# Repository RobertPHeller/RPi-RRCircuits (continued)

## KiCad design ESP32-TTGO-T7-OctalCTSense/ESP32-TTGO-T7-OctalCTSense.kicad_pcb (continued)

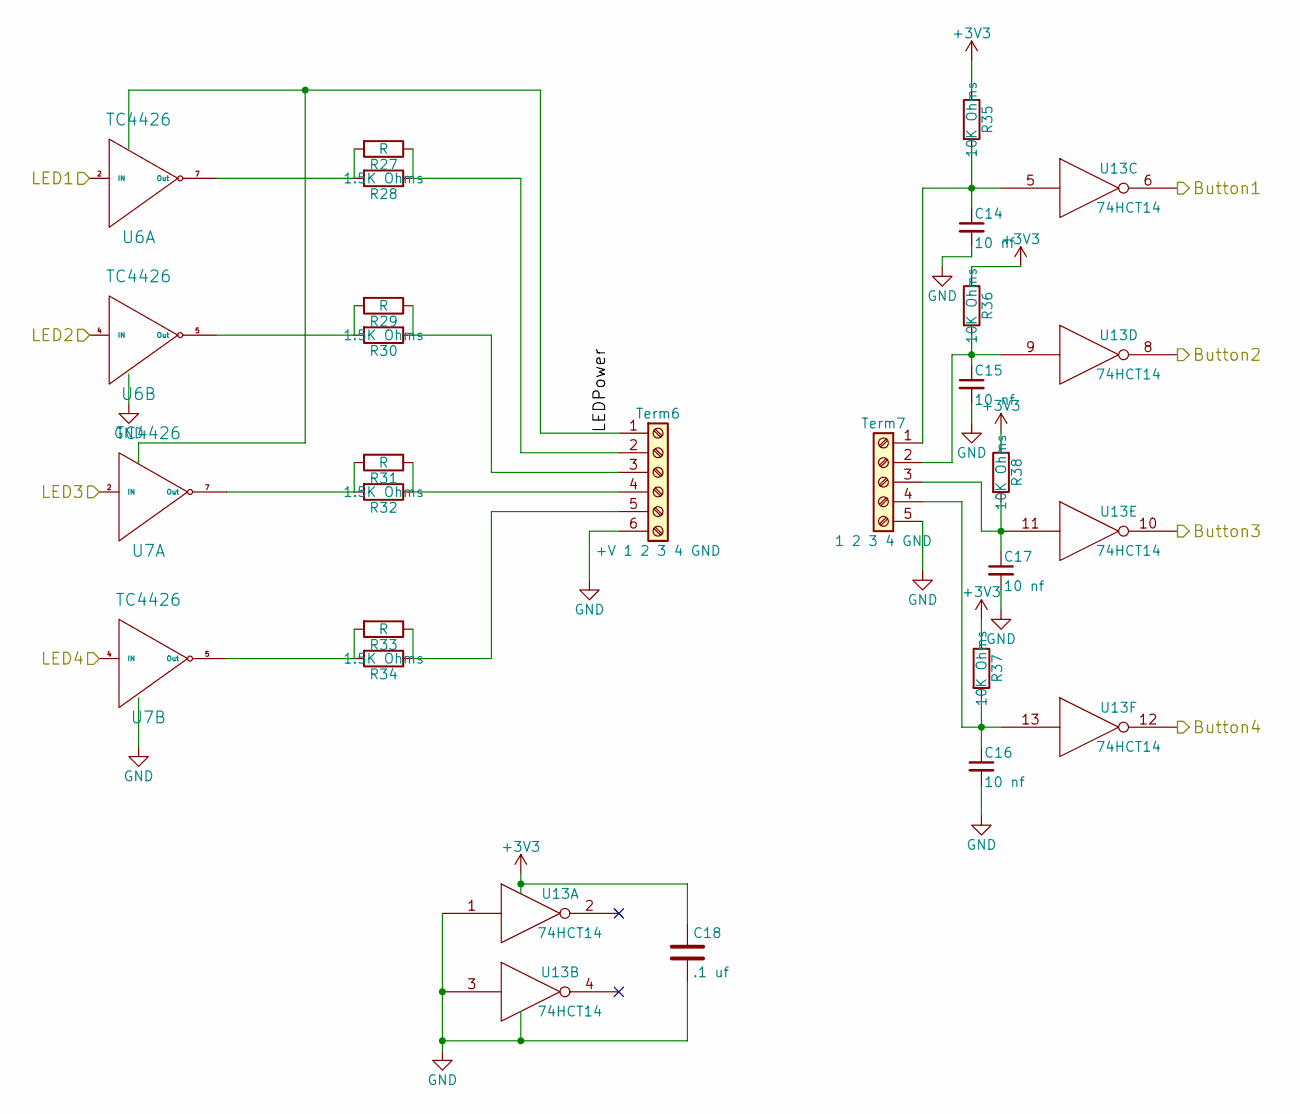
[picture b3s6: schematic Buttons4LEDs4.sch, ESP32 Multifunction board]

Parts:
C14, C15, C16, C17: 10 nf; C_0603; Mouser Part Number 710-885382206002
C18: .1 uf; C_0603
R27, R29, R31, R33: R; R_Axial_DIN0207_L6.3mm_D2.5mm_P7.62mm_Horizontal
R28, R30, R32, R34: 1.5K Ohms; R_0603; Mouser Part Number 71-CRCW06031K50JNEAC
R35, R36, R37, R38: 10K Ohms; R_0603; Mouser Part Number 71-CRCW060310K0JNEBC
Term6: +V 1 2 3 4 GND; TerminalBlock_Pheonix_MPT-2.54mm_6pol; Mouser Part Number 651-1725698
Term7: 1 2 3 4 GND; TerminalBlock_Pheonix_MPT-2.54mm_5pol; Mouser Part Number 651-1725685
U6, U7: TC4426; SOIC-8_3.9x4.9mm_Pitch1.27mm
U13: 74HCT14; SOIC-14_3.9x8.7mm_Pitch1.27mm; Mouser Part Number 595-CD74HC14M

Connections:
/Button_1: U13.6; also elsewhere on the board
/Button_2: U13.8; also elsewhere on the board
/Button_3: U13.10; also elsewhere on the board
/Button_4: U13.12; also elsewhere on the board
/LED_1: U6.2 (IN); also elsewhere on the board
/LED_2: U6.4 (IN); also elsewhere on the board
/LED_3: U7.2 (IN); also elsewhere on the board
/LED_4: U7.4 (IN); also elsewhere on the board
GND: C14.2, C15.2, C16.2, C17.2, C18.2, Term6.6, Term7.5, U6.3 (GND), U7.3 (GND), U13.1, U13.3, U13.7 (GND); also elsewhere on the board
unnamed: C14.1, R35.2, Term7.1, U13.5
unnamed: C15.1, R36.2, Term7.2, U13.9
unnamed: C16.1, R37.2, Term7.4, U13.13
unnamed: C17.1, R38.2, Term7.3, U13.11
unnamed: R27.1, R28.1, Term6.2
unnamed: R27.2, R28.2, U6.7 (Out)
unnamed: R29.1, R30.1, Term6.3
unnamed: R29.2, R30.2, U6.5 (Out)
unnamed: R31.1, R32.1, Term6.4
unnamed: R31.2, R32.2, U7.7 (Out)
unnamed: R33.1, R34.1, Term6.5
unnamed: R33.2, R34.2, U7.5 (Out)
Vdd: Term6.1, U6.6 (Vdd), U7.6 (Vdd)

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
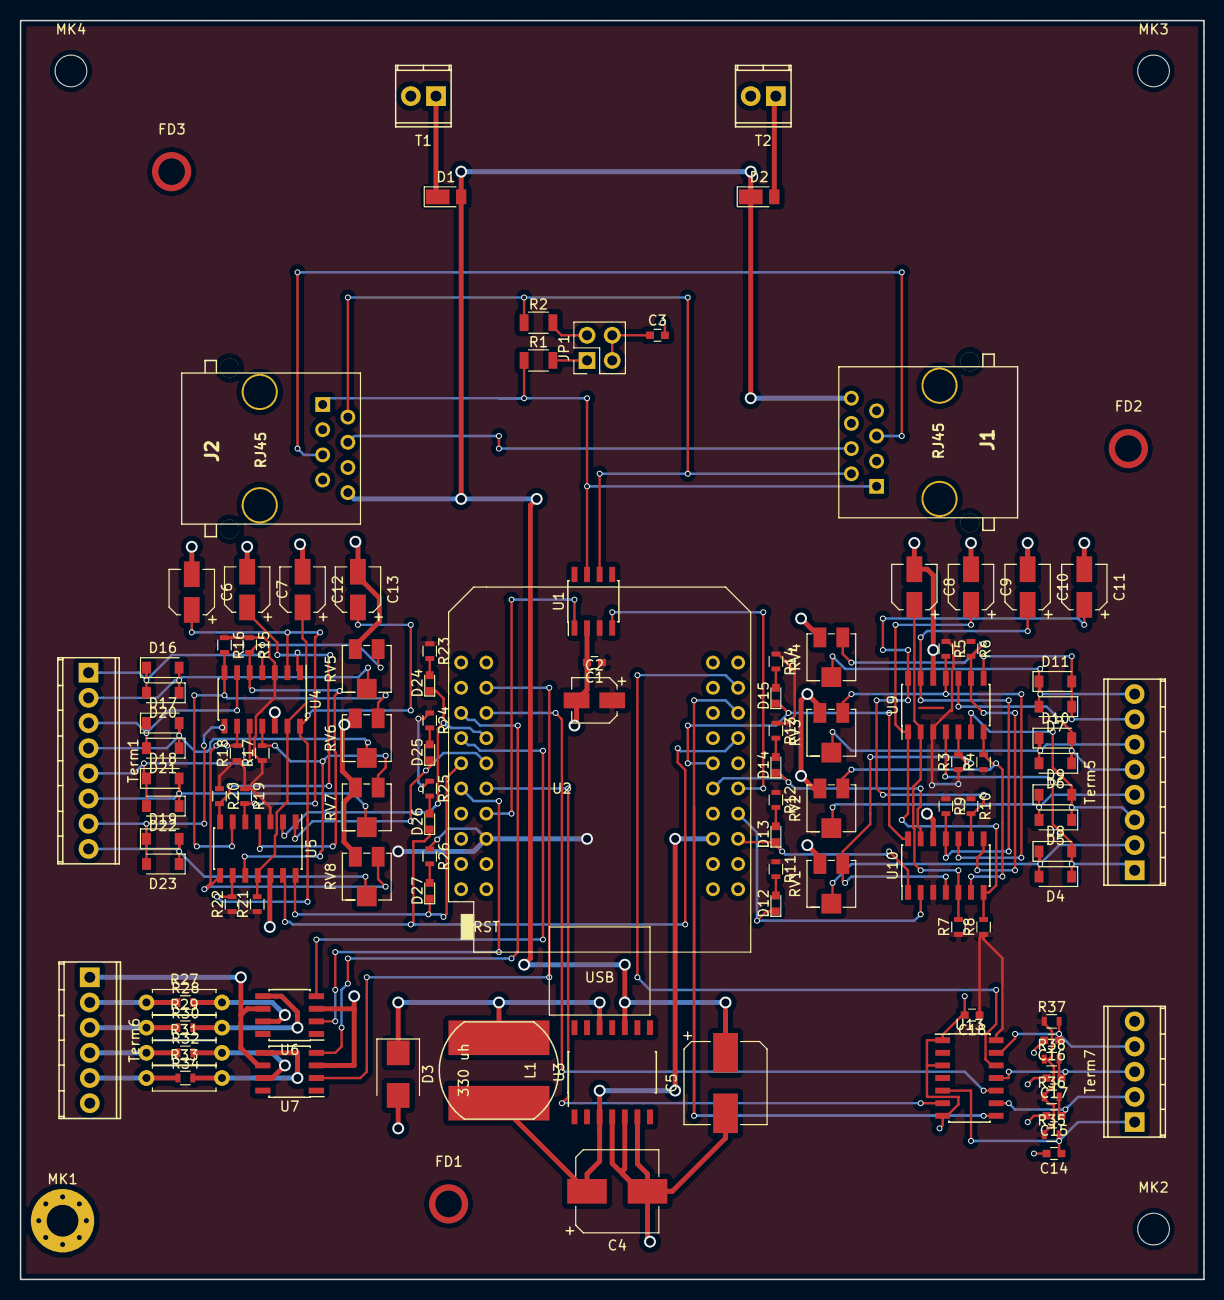
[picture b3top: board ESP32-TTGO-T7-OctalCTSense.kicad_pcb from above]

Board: 2 copper layers, 119.4 x 127.0 mm, 118 parts (0 on the bottom side), 85 nets.

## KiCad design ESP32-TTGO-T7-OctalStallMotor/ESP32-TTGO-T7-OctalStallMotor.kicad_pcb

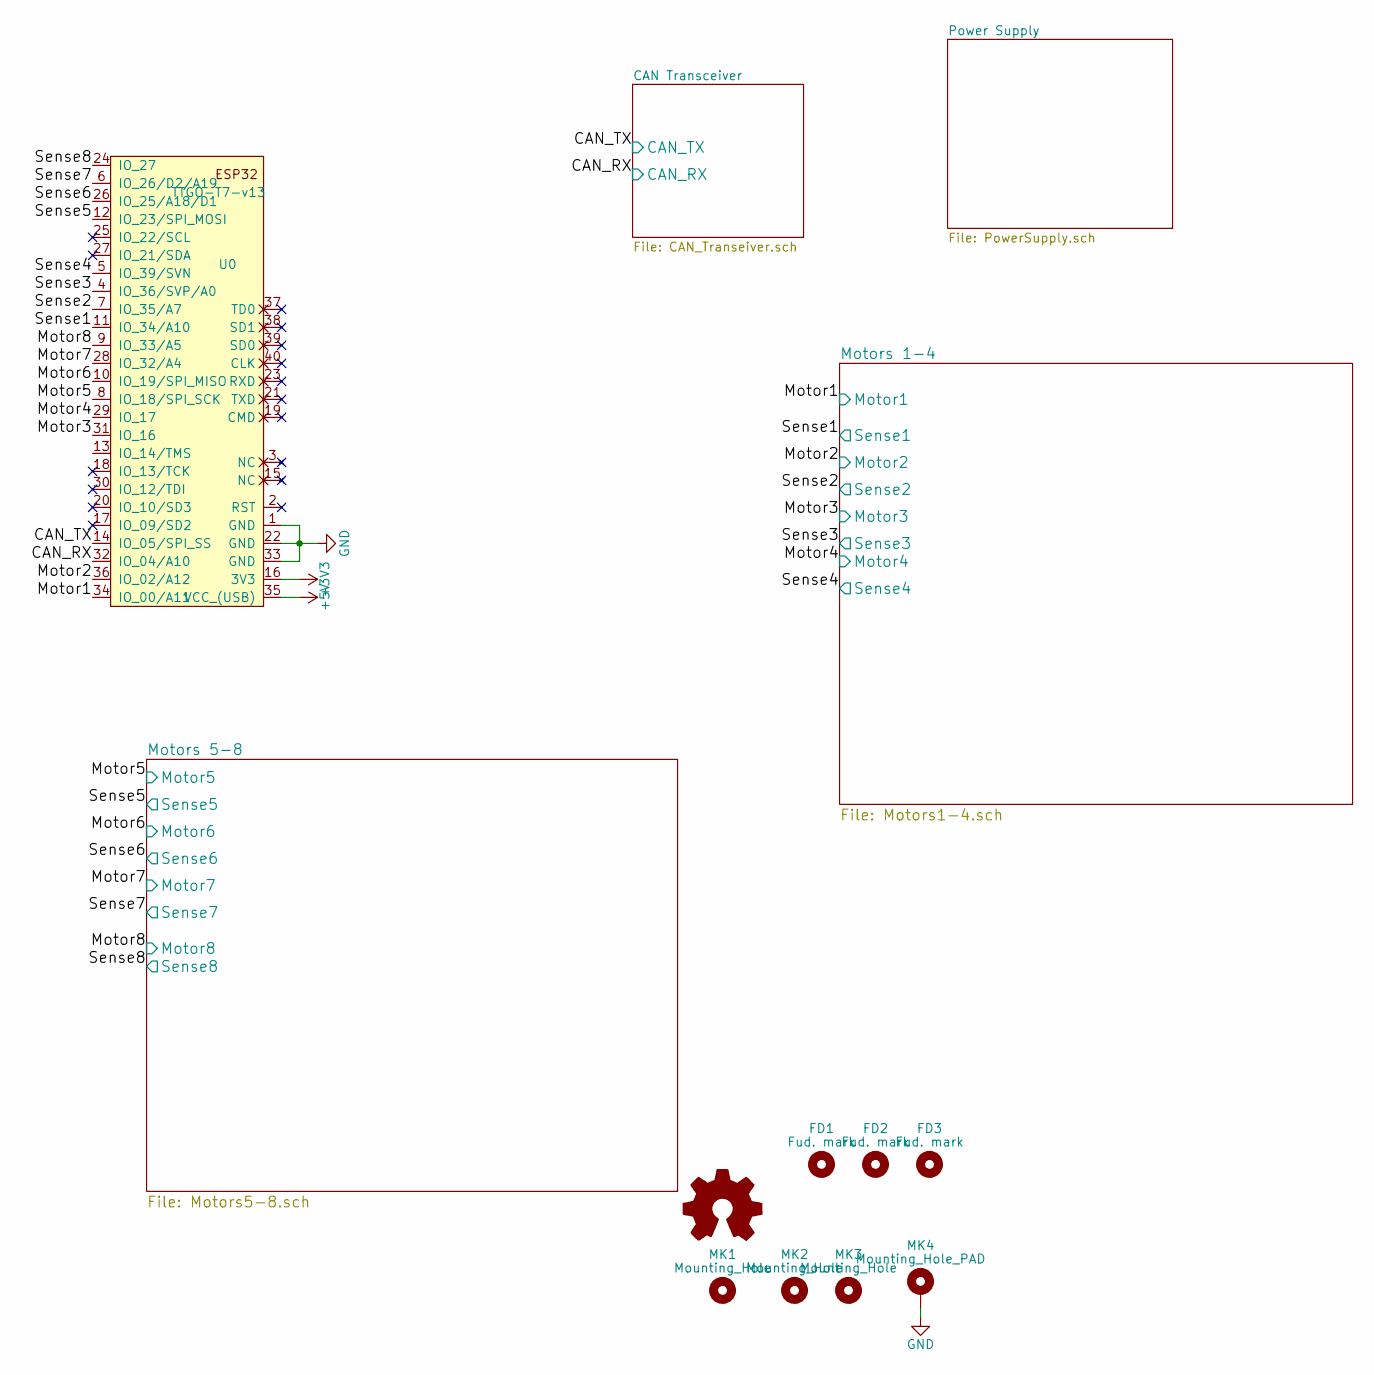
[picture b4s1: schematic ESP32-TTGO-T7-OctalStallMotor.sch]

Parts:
FD1, FD2, FD3: Fud. mark; Fiducial_Modern_CopperTop
MK1, MK2, MK3: Mounting_Hole; MountingHole_3.2mm_M3
MK4: Mounting_Hole_PAD; MountingHole_3.2mm_M3_Pad_Via
U0: TTGO-T7-v13; ESP32_mini

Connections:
+5V: U0.35 (VCC_(USB)); also elsewhere on the board
/CAN_RX: U0.32 (IO_04/A10); also elsewhere on the board
/CAN_TX: U0.14 (IO_05/SPI_SS); also elsewhere on the board
/Motor1: U0.34 (IO_00/A11); also elsewhere on the board
/Motor2: U0.36 (IO_02/A12); also elsewhere on the board
/Motor3: U0.31 (IO_16); also elsewhere on the board
/Motor4: U0.29 (IO_17); also elsewhere on the board
/Motor5: U0.8 (IO_18/SPI_SCK); also elsewhere on the board
/Motor6: U0.10 (IO_19/SPI_MISO); also elsewhere on the board
/Motor7: U0.28 (IO_32/A4); also elsewhere on the board
/Motor8: U0.9 (IO_33/A5); also elsewhere on the board
/Sense1: U0.11 (IO_34/A10); also elsewhere on the board
/Sense2: U0.7 (IO_35/A7); also elsewhere on the board
/Sense3: U0.4 (IO_36/SVP/A0); also elsewhere on the board
/Sense4: U0.5 (IO_39/SVN); also elsewhere on the board
/Sense5: U0.12 (IO_23/SPI_MOSI); also elsewhere on the board
/Sense6: U0.26 (IO_25/A18/D1); also elsewhere on the board
/Sense7: U0.6 (IO_26/D2/A19); also elsewhere on the board
/Sense8: U0.24 (IO_27); also elsewhere on the board
GND: MK4.1, U0.1 (GND), U0.22 (GND), U0.33 (GND); also elsewhere on the board

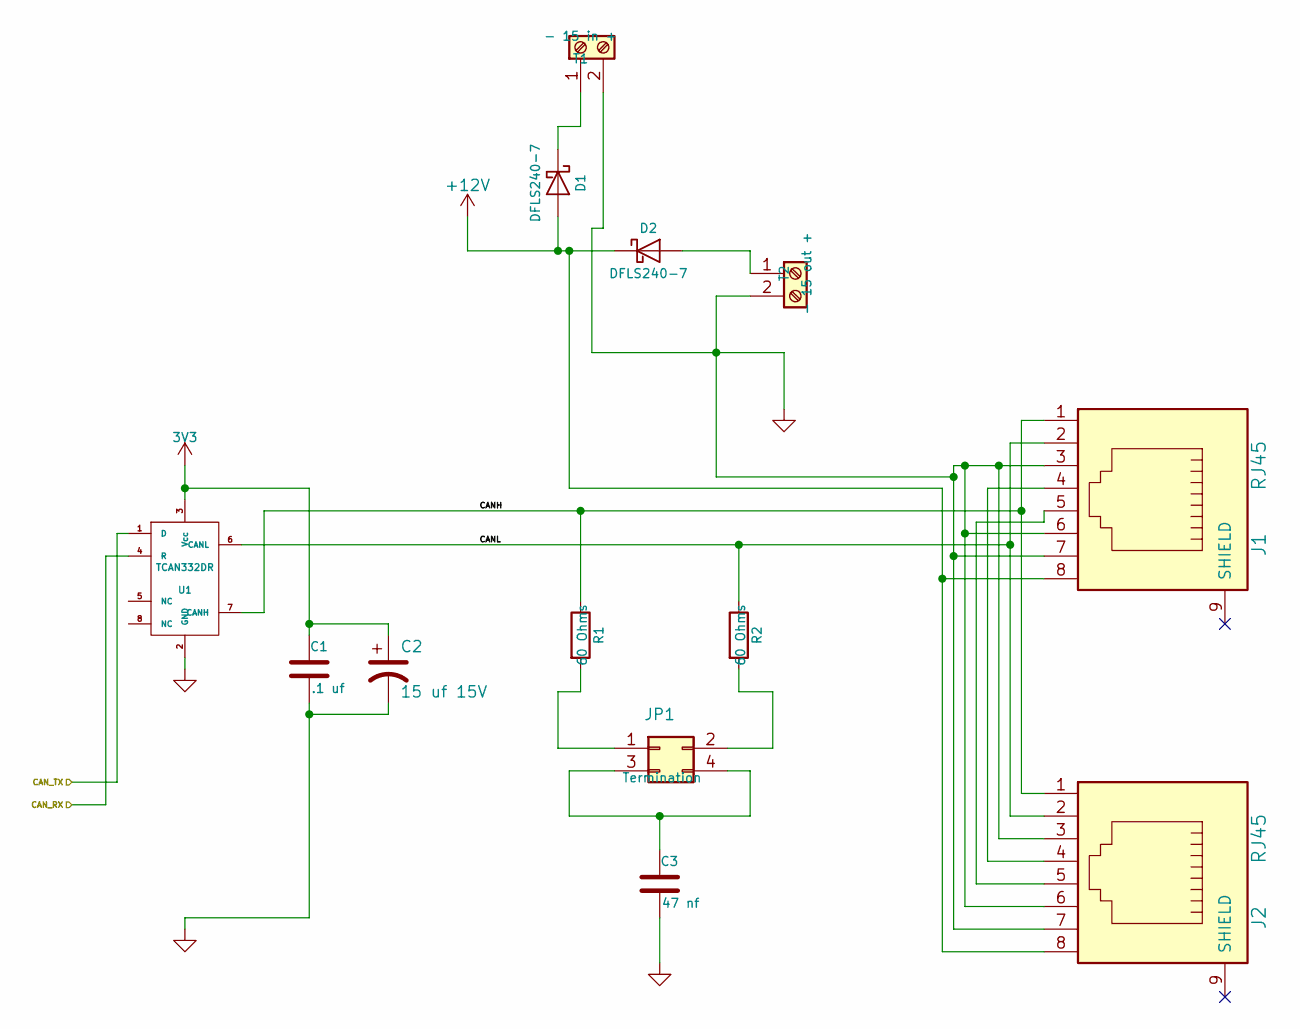
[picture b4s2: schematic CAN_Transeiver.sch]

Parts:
C1: .1 uf; C_0603; Mouser Part Number 710-885012206095
C2: 15 uf 15V; CP_Elec_4x5.7; Mouser Part Number 647-UUD1C150MCL
C3: 47 nf; C_0603; Mouser Part Number 710-885012206093
D1, D2: DFLS240-7; D_PowerDI-123; Mouser Part Number 621-DFLS240-7
J1, J2: RJ45; RJ45_8N-S; Mouser Part Number 710-615008144221
JP1: Termination; Pin_Header_Straight_2x02_Pitch2.54mm; Mouser Part Number 649-67997-404HLF
R1, R2: 60 Ohms; R_1206; Mouser Part Number 71-CRCW120660R0KNAIF
T1: - 15 in +; TerminalBlock_Pheonix_MPT-2.54mm_2pol; Mouser Part Number 651-1725656
T2: - 15 out +; TerminalBlock_Pheonix_MPT-2.54mm_2pol; Mouser Part Number 651-1725656
U1: TCAN332DR; SOIC-8_3.9x4.9mm_Pitch1.27mm; Mouser Part Number 595-TCAN332DR

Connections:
+12V: D1.2 (A), D2.1 (K), J1.8, J2.8; also elsewhere on the board
/CAN Transceiver/CANH: J1.1, J2.1, R1.1, U1.7 (CANH)
/CAN Transceiver/CANL: J1.2, J2.2, R2.1, U1.6 (CANL)
/CAN_RX: U1.4 (R); also elsewhere on the board
/CAN_TX: U1.1 (D); also elsewhere on the board
GND: C1.2, C2.2, C3.2, J1.3, J1.6, J1.7, J2.3, J2.6, J2.7, T1.2, T2.2, U1.2 (GND); also elsewhere on the board
unnamed: C3.1, JP1.3, JP1.4
unnamed: D1.1 (K), T1.1
unnamed: D2.2 (A), T2.1
unnamed: J1.4, J2.4
unnamed: J1.5, J2.5
unnamed: JP1.1, R1.2
unnamed: JP1.2, R2.2

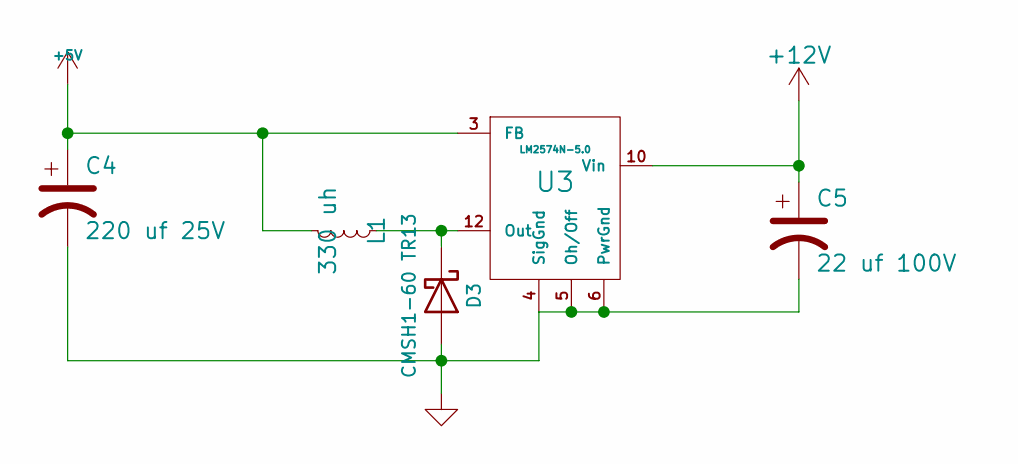
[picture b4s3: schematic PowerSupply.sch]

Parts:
C4: 220 uf 25V; CP_Elec_8x10; Mouser Part Number 647-UWT1E221MNL1GS
C5: 22 uf 100V; CP_Elec_8x10; Mouser Part Number 647-UUX2A220MNL6GS
D3: CMSH1-60 TR13; D_SMB; Mouser Part Number 610-CMSH1-60TR13
L1: 330 uh; SRN1060; Mouser Part Number 652-SRN1060-331M
U3: LM2574N-5.0; SOIC-14_7.4x8.7mm_Pitch1.27mm; Mouser Part Number 926-LM2574N-5.0/NOPB

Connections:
+5V: C4.1, L1.2, U3.3 (FB); also elsewhere on the board
+12V: C5.1, U3.10 (Vin); also elsewhere on the board
GND: C4.2, C5.2, D3.2 (A), U3.4 (SigGnd), U3.5 (Oh/Off), U3.6 (PwrGnd); also elsewhere on the board
unnamed: D3.1 (K), L1.1, U3.12 (Out)

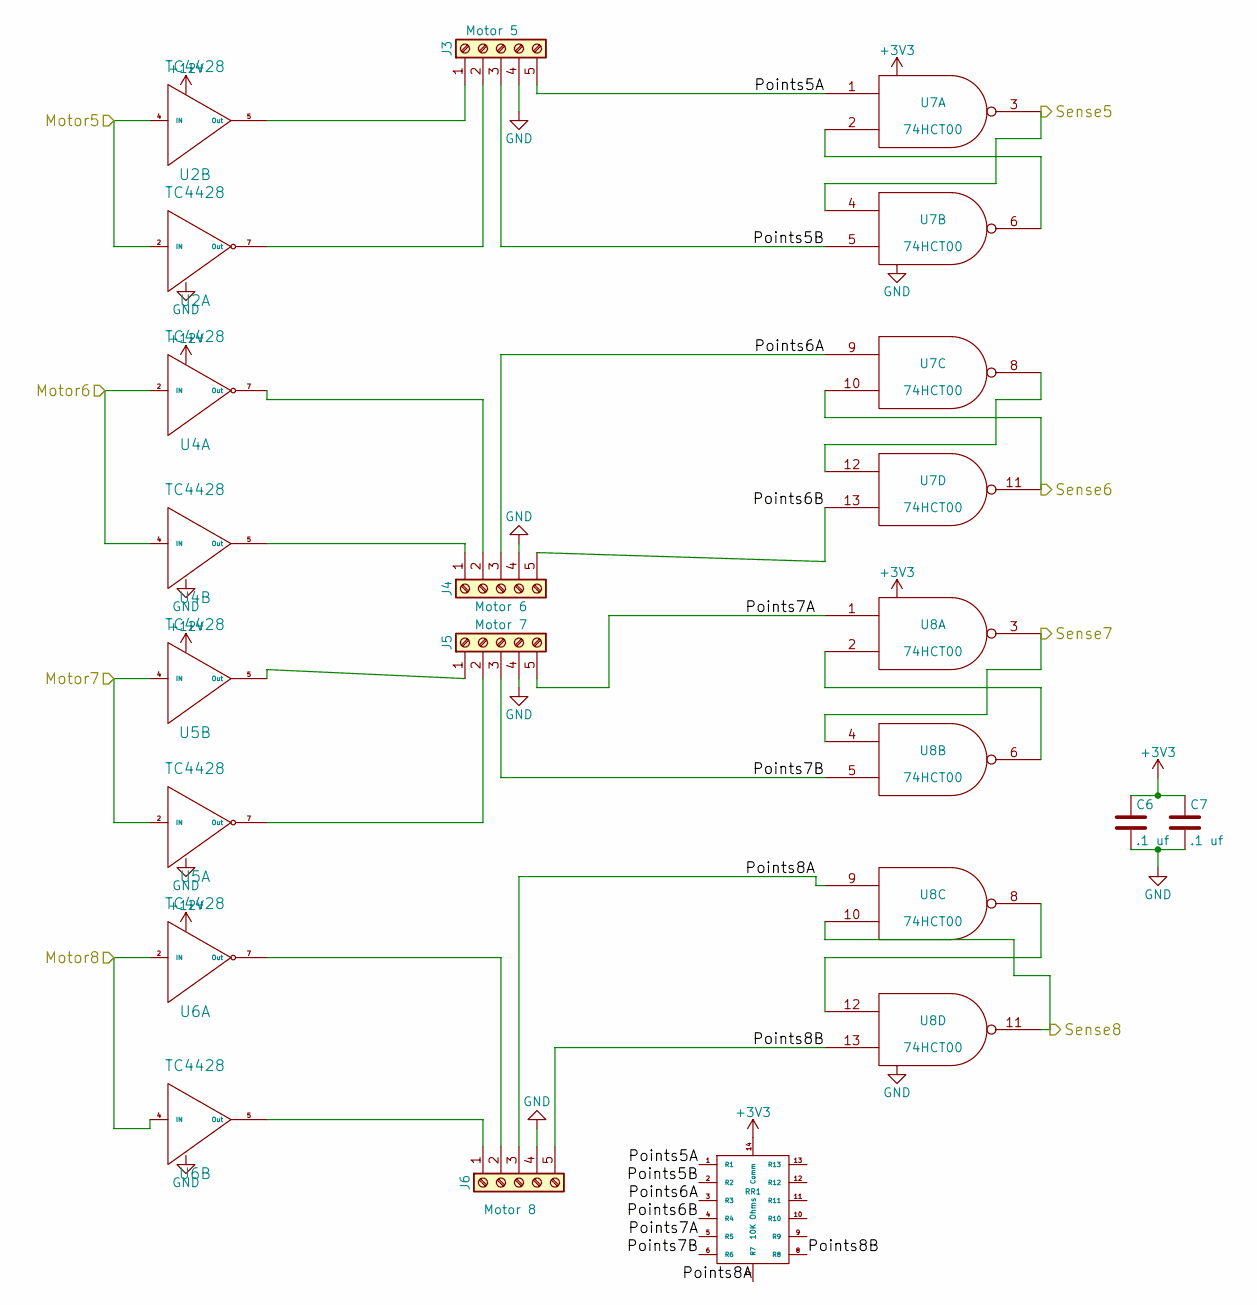
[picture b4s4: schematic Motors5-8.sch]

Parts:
C6, C7: .1 uf; C_0603; Mouser Part Number 710-885012206095
J3: Motor 5; TerminalBlock_Pheonix_MPT-2.54mm_5pol; Mouser Part Number 651-1725685
J4: Motor 6; TerminalBlock_Pheonix_MPT-2.54mm_5pol; Mouser Part Number 651-1725685
J5: Motor 7; TerminalBlock_Pheonix_MPT-2.54mm_5pol; Mouser Part Number 651-1725685
J6: Motor 8; TerminalBlock_Pheonix_MPT-2.54mm_5pol; Mouser Part Number 651-1725685
RR1: 10K Ohms; 4814P; Mouser Part Number 652-4814P-T2LF-10K
U2, U5: TC4428; SOIC-8_3.9x4.9mm_Pitch1.27mm; Mouser Part Number 579-TC4428VOA
U4, U6: TC4428; SOIC-8_3.9x4.9mm_Pitch1.27mm
U7, U8: 74HCT00; SOIC-14_3.9x8.7mm_Pitch1.27mm; Mouser Part Number 595-SN74AHC00D

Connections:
+12V: U2.6 (Vdd), U4.6 (Vdd), U5.6 (Vdd), U6.6 (Vdd); also elsewhere on the board
/Motor5: U2.2 (IN), U2.4 (IN); also elsewhere on the board
/Motor6: U4.2 (IN), U4.4 (IN); also elsewhere on the board
/Motor7: U5.2 (IN), U5.4 (IN); also elsewhere on the board
/Motor8: U6.2 (IN), U6.4 (IN); also elsewhere on the board
/Motors 5-8/Points5A: J3.5, RR1.1 (R1), U7.1
/Motors 5-8/Points5B: J3.3, RR1.2 (R2), U7.5
/Motors 5-8/Points6A: J4.3, RR1.3 (R3), U7.9
/Motors 5-8/Points6B: J4.5, RR1.4 (R4), U7.13
/Motors 5-8/Points7A: J5.5, RR1.5 (R5), U8.1
/Motors 5-8/Points7B: J5.3, RR1.6 (R6), U8.5
/Motors 5-8/Points8A: J6.3, RR1.7 (R7), U8.9
/Motors 5-8/Points8B: J6.5, RR1.8 (R8), U8.13
/Sense5: U7.3, U7.4; also elsewhere on the board
/Sense6: U7.10, U7.11; also elsewhere on the board
/Sense7: U8.3, U8.4; also elsewhere on the board
/Sense8: U8.10, U8.11; also elsewhere on the board
GND: C6.2, C7.2, J3.4, J4.4, J5.4, J6.4, U2.3 (GND), U4.3 (GND), U5.3 (GND), U6.3 (GND), U7.7 (GND), U8.7 (GND); also elsewhere on the board
unnamed: J3.1, U2.5 (Out)
unnamed: J3.2, U2.7 (Out)
unnamed: J4.1, U4.5 (Out)
unnamed: J4.2, U4.7 (Out)
unnamed: J5.1, U5.5 (Out)
unnamed: J5.2, U5.7 (Out)
unnamed: J6.1, U6.5 (Out)
unnamed: J6.2, U6.7 (Out)
unnamed: U7.2, U7.6
unnamed: U7.8, U7.12
unnamed: U8.2, U8.6
unnamed: U8.8, U8.12

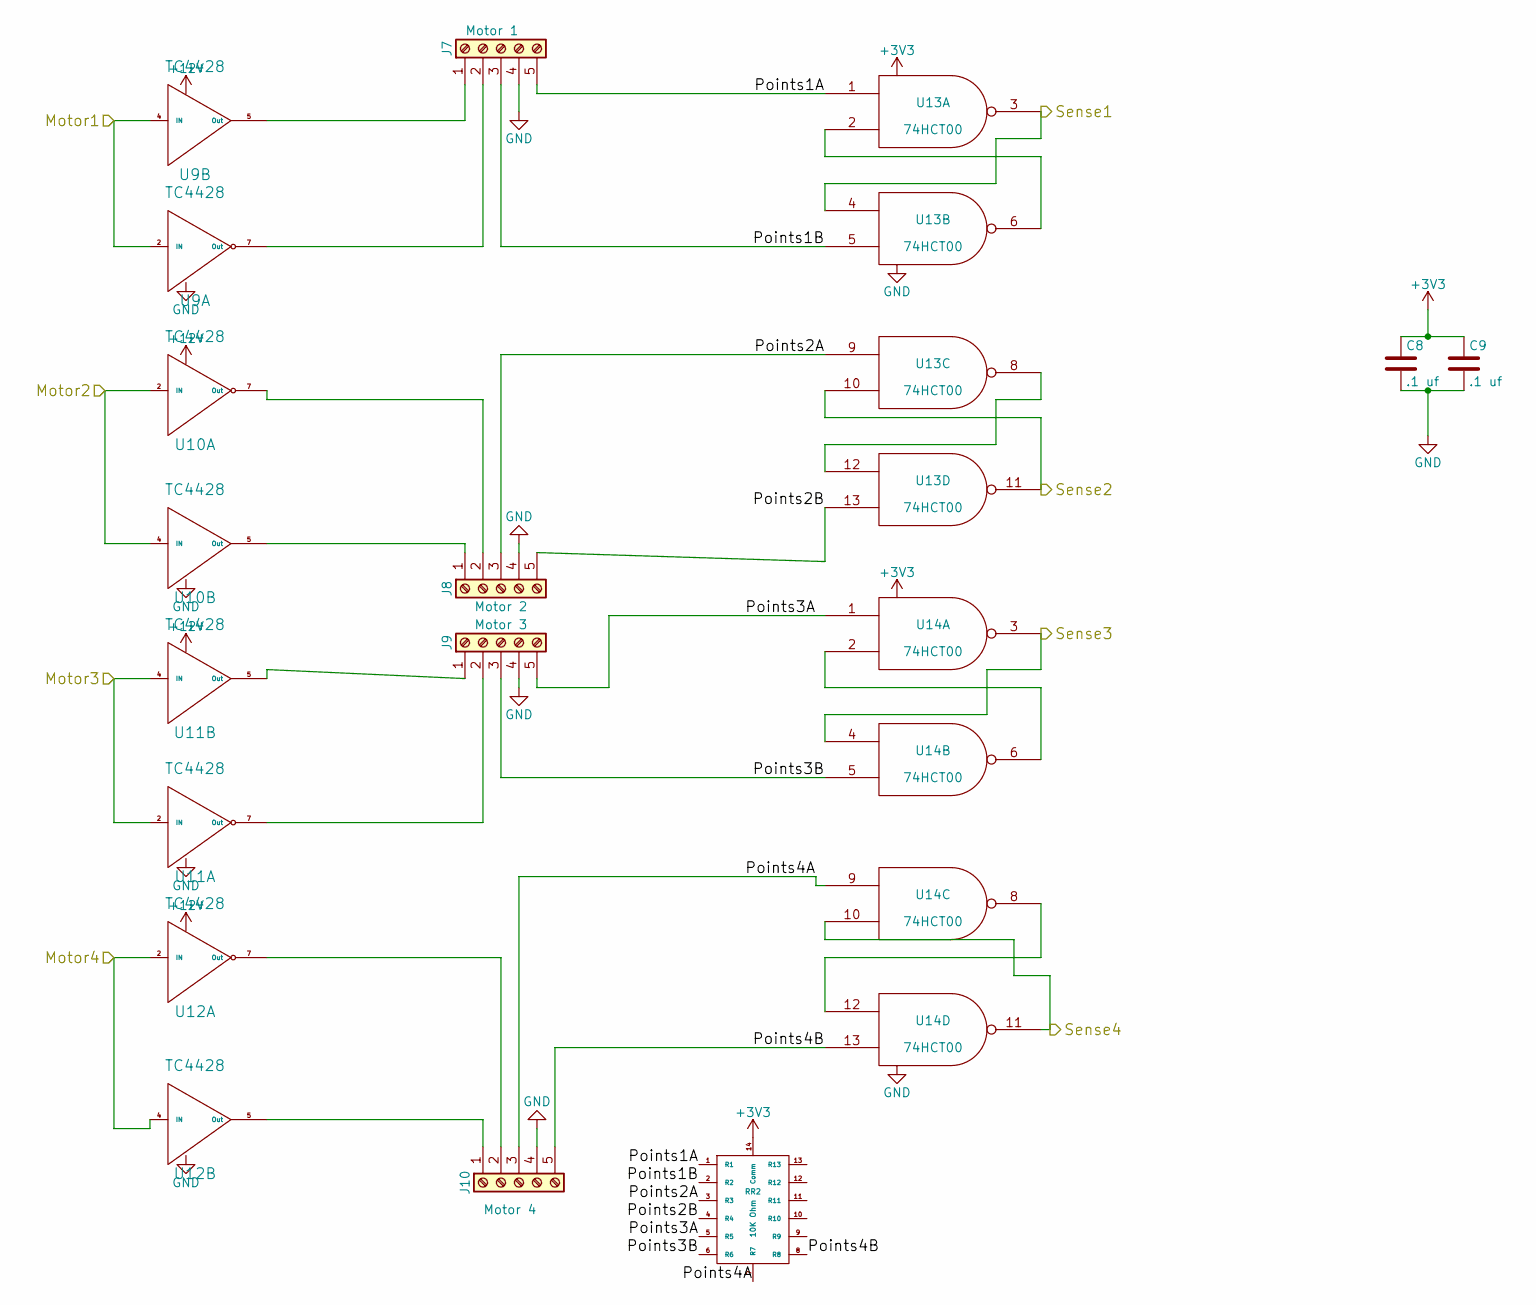
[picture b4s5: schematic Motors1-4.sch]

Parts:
C8, C9: .1 uf; C_0603; Mouser Part Number 710-885012206095
J7: Motor 1; TerminalBlock_Pheonix_MPT-2.54mm_5pol; Mouser Part Number 651-1725685
J8: Motor 2; TerminalBlock_Pheonix_MPT-2.54mm_5pol; Mouser Part Number 651-1725685
J9: Motor 3; TerminalBlock_Pheonix_MPT-2.54mm_5pol; Mouser Part Number 651-1725685
J10: Motor 4; TerminalBlock_Pheonix_MPT-2.54mm_5pol; Mouser Part Number 651-1725685
RR2: 10K Ohm; 4814P; Mouser Part Number 652-4814P-T2LF-10K
U9, U11: TC4428; SOIC-8_3.9x4.9mm_Pitch1.27mm; Mouser Part Number 579-TC4428VOA
U10, U12: TC4428; SOIC-8_3.9x4.9mm_Pitch1.27mm
U13, U14: 74HCT00; SOIC-14_3.9x8.7mm_Pitch1.27mm; Mouser Part Number 595-SN74AHC00D

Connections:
+12V: U9.6 (Vdd), U10.6 (Vdd), U11.6 (Vdd), U12.6 (Vdd); also elsewhere on the board
/Motor1: U9.2 (IN), U9.4 (IN); also elsewhere on the board
/Motor2: U10.2 (IN), U10.4 (IN); also elsewhere on the board
/Motor3: U11.2 (IN), U11.4 (IN); also elsewhere on the board
/Motor4: U12.2 (IN), U12.4 (IN); also elsewhere on the board
/Motors 1-4/Points1A: J7.5, RR2.1 (R1), U13.1
/Motors 1-4/Points1B: J7.3, RR2.2 (R2), U13.5
/Motors 1-4/Points2A: J8.3, RR2.3 (R3), U13.9
/Motors 1-4/Points2B: J8.5, RR2.4 (R4), U13.13
/Motors 1-4/Points3A: J9.5, RR2.5 (R5), U14.1
/Motors 1-4/Points3B: J9.3, RR2.6 (R6), U14.5
/Motors 1-4/Points4A: J10.3, RR2.7 (R7), U14.9
/Motors 1-4/Points4B: J10.5, RR2.8 (R8), U14.13
/Sense1: U13.3, U13.4; also elsewhere on the board
/Sense2: U13.10, U13.11; also elsewhere on the board
/Sense3: U14.3, U14.4; also elsewhere on the board
/Sense4: U14.10, U14.11; also elsewhere on the board
GND: C8.2, C9.2, J7.4, J8.4, J9.4, J10.4, U9.3 (GND), U10.3 (GND), U11.3 (GND), U12.3 (GND), U13.7 (GND), U14.7 (GND); also elsewhere on the board
unnamed: J7.1, U9.5 (Out)
unnamed: J7.2, U9.7 (Out)
unnamed: J8.1, U10.5 (Out)
unnamed: J8.2, U10.7 (Out)
unnamed: J9.1, U11.5 (Out)
unnamed: J9.2, U11.7 (Out)
unnamed: J10.1, U12.5 (Out)
unnamed: J10.2, U12.7 (Out)
unnamed: U13.2, U13.6
unnamed: U13.8, U13.12
unnamed: U14.2, U14.6
unnamed: U14.8, U14.12

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
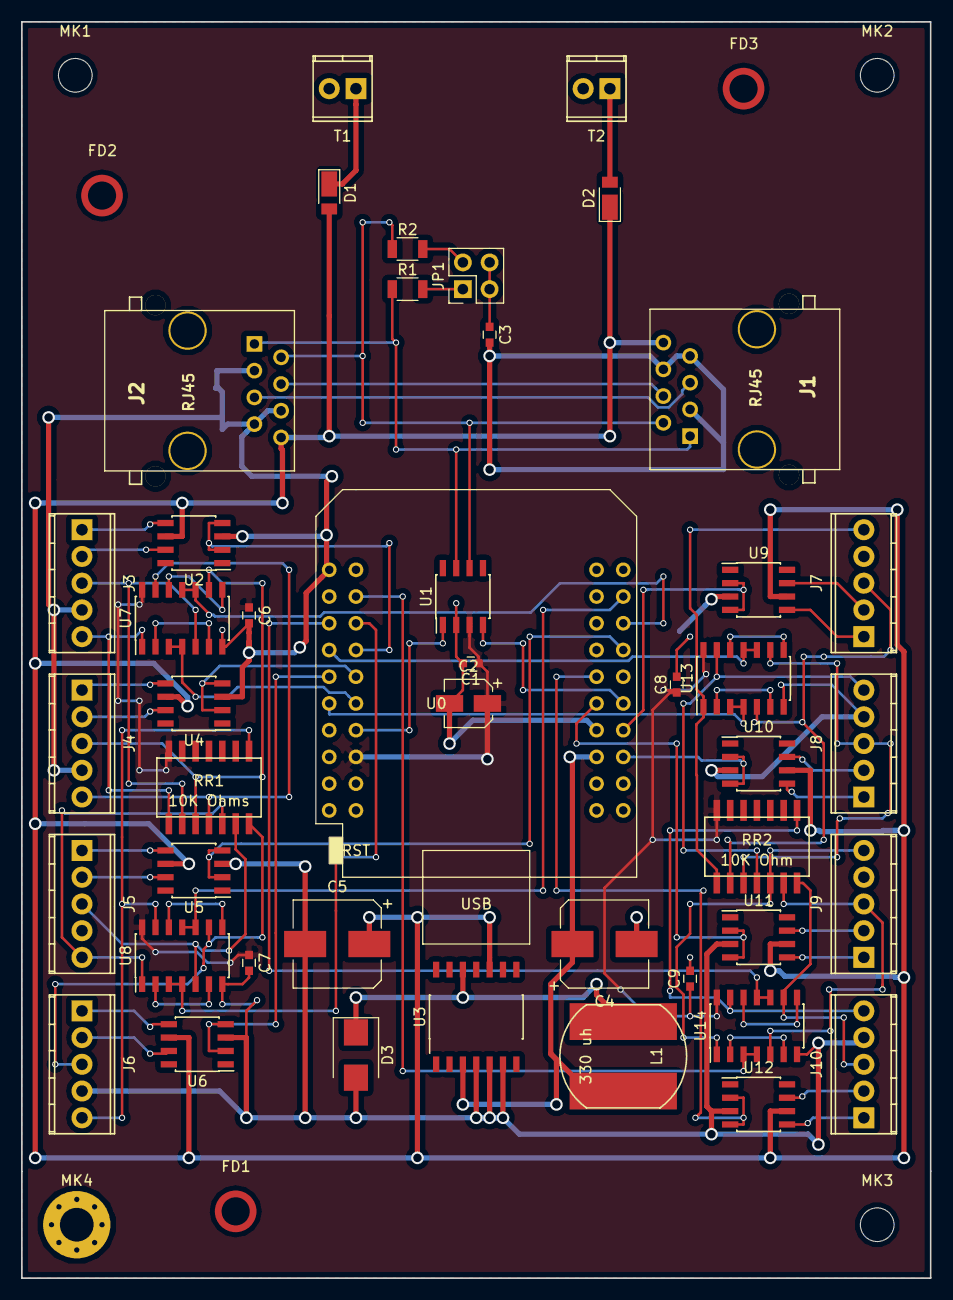
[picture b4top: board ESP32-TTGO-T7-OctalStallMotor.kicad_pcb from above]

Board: 2 copper layers, 86.4 x 119.4 mm, 52 parts (0 on the bottom side), 72 nets.
